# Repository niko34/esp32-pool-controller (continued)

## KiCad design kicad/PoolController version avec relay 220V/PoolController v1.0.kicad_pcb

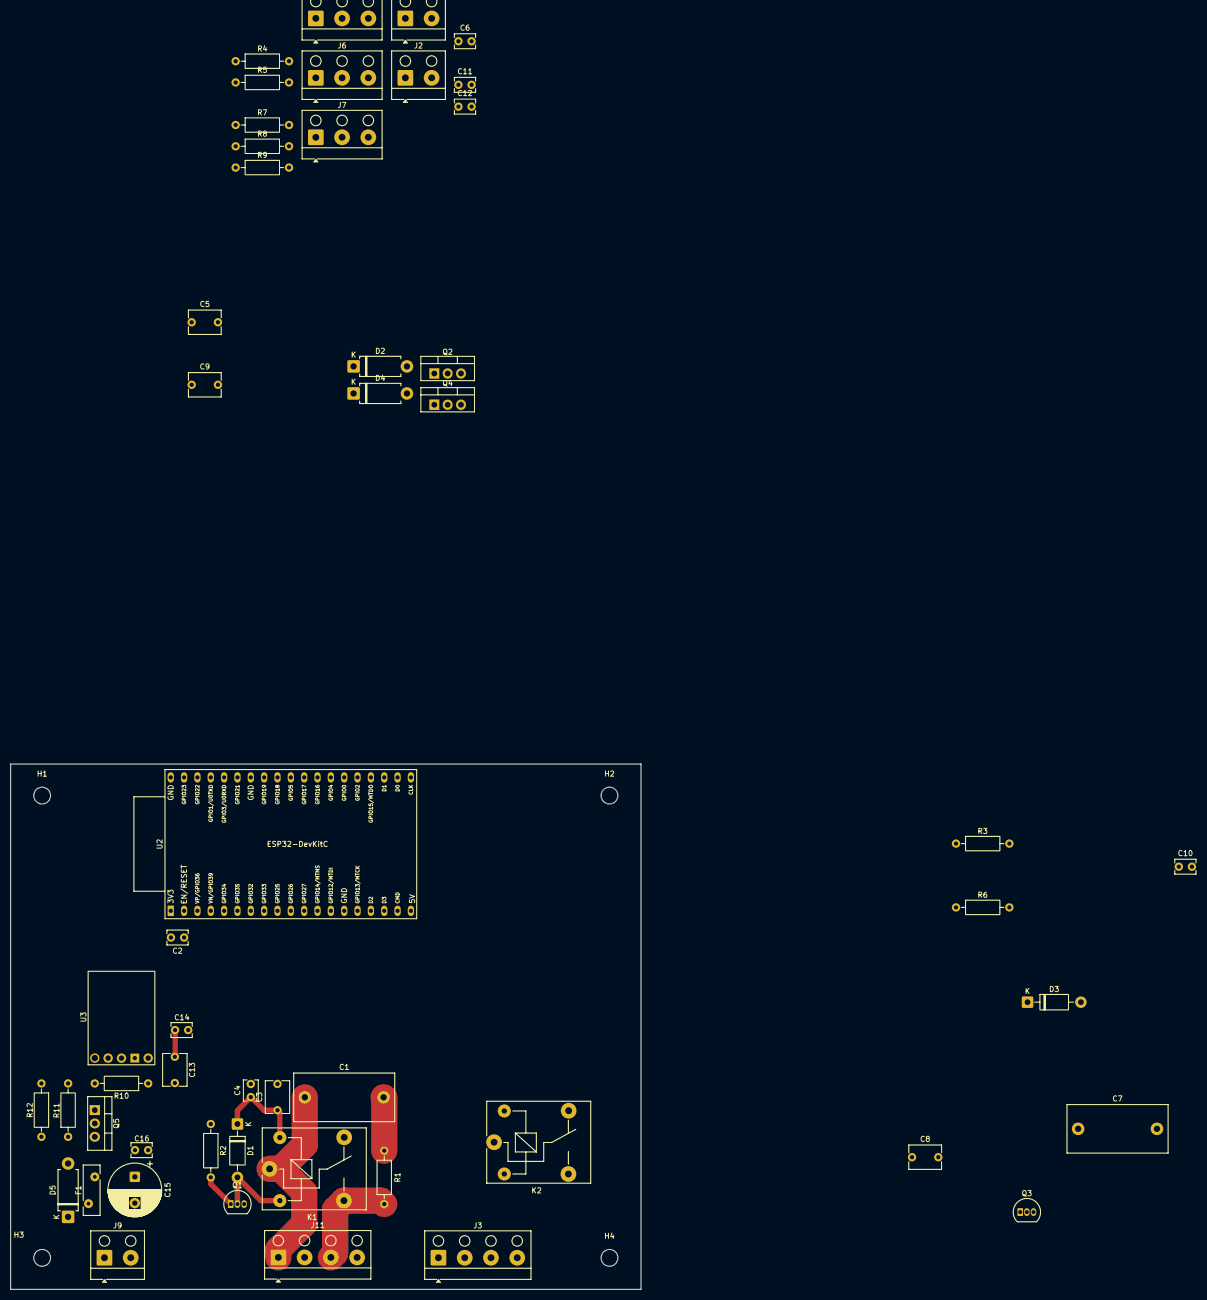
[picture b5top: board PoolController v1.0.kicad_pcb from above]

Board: 2 copper layers, 120.0 x 100.0 mm, 55 parts (0 on the bottom side), 29 nets.

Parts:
C1, C7: PME271MB6100MR30; C_Rect_L19.0mm_W9.0mm_P15.00mm_MKS4
C2, C4, C6, C10, C11, C12, C14, C16: 100nF; C_Disc_D3.8mm_W2.6mm_P2.50mm
C3, C5, C8, C9, C13: 10 µF; C_Disc_D6.0mm_W4.4mm_P5.00mm
C15: 470µF; CP_Radial_D10.0mm_P5.00mm
D1, D3: 1N4007; D_DO-41_SOD81_P10.16mm_Horizontal
D2, D4: 1N5819; D_DO-15_P10.16mm_Horizontal
D5: P6KE13A; D_DO-15_P10.16mm_Horizontal
F1: FX200-16; Fuse_Bourns_MF-RHT200
H1, H2, H3, H4: MountingHole; MountingHole_3.2mm_M3
J1, J2: Pompe Péristaltique; Altech_AK100_1x02_P5.00mm
J3, J11: Eclairage; Altech_AK100_1x04_P5.00mm
J4: Sonde température DS18B20; Altech_AK100_1x03_P5.00mm
J6, J7: Conn_01x03; Altech_AK100_1x03_P5.00mm
J9: Alimentation 12V (2A min); Altech_AK100_1x02_P5.00mm
K1, K2: SANYOU_SRD_Form_C; Relay_SPDT_SANYOU_SRD_Series_Form_C
Q1, Q3: PN2222A; TO-92_Inline
Q2, Q4: IRLZ44N; TO-220-3_Vertical
Q5: IRF4905; TO-220-3_Vertical
R1, R3, R4, R7: 100Ω; R_Axial_DIN0207_L6.3mm_D2.5mm_P10.16mm_Horizontal
R2, R6: 330Ω; R_Axial_DIN0207_L6.3mm_D2.5mm_P10.16mm_Horizontal
R5, R8, R10, R12: 10KΩ; R_Axial_DIN0207_L6.3mm_D2.5mm_P10.16mm_Horizontal
R9: 4.7KΩ; R_Axial_DIN0207_L6.3mm_D2.5mm_P10.16mm_Horizontal
R11: 10Ω; R_Axial_DIN0207_L6.3mm_D2.5mm_P10.16mm_Horizontal
U2: ESP32-DevKitC
U3: D24V10F3; Pololu_D24V10F3

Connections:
+3.3V: C2.2, C3.1, C4.1, C8.1, C10.1, C12.2, C13.1, C14.1, D1.1 (K), D3.1 (K), J4.2, J6.1, J7.1, K1.5, K2.5, R9.1, U2.1 (3V3), U3.5 (VOUT)
+12V: C5.1, C6.1, C9.1, C11.1, D2.1 (K), D4.1 (K), F1.1, J1.1, J2.1, J9.1, Q5.2 (D), R10.1, U3.3 (VIN)
/230V_IN_ECLAIRAGE: C1.1, J11.1, K1.1
/230V_IN_FILTRATION: C7.1, J3.1, K2.1
/230V_OUT_ECLAIRAGE: J11.3, K1.3, R1.1
/230V_OUT_FILTRATION: J3.3, K2.3, R3.1
/DATA_DS18B20: J4.3, R9.2, U2.5 (VDET_1/GPIO34/ADC1_CH6)
/DATA_ORP: J7.3, U2.8 (32K_XN/GPIO33/ADC1_CH5)
/DATA_PH: J6.3, U2.7 (32K_XP/GPIO32/ADC1_CH4)
/POMPE_1: R4.2, U2.15 (MTCK/GPIO13/ADC2_CH4)
/POMPE_2: R7.2, U2.12 (MTMS/GPIO14/ADC2_CH6)
/RELAIS_1: R2.1, U2.10 (DAC_2/ADC2_CH9/GPIO26)
/RELAIS_2: R6.1, U2.11 (ADC2_CH7/GPIO27)
GND: C2.1, C3.2, C4.2, C5.2, C6.2, C8.2, C9.2, C10.2, C11.2, C12.1, C13.2, C14.2, C15.2, C16.2, D5.1 (A1), J4.1, J6.2, J7.2, J9.2, Q1.3 (C), Q2.3 (S), Q3.3 (C), Q4.3 (S), R5.2, R8.2, R12.2, U2.14 (GND), U2.32 (GND), U2.38 (GND), U3.4 (GND)
unnamed: C1.2, R1.2
unnamed: C7.2, R3.2
unnamed: D1.2 (A), K1.2, Q1.2 (B)
unnamed: D2.2 (A), J1.2, Q2.2 (D)
unnamed: D3.2 (A), K2.2, Q3.2 (B)
unnamed: D4.2 (A), J2.2, Q4.2 (D)
unnamed: C15.1, C16.1, D5.2 (A2), F1.2, Q5.3 (S), R11.1
unnamed: J3.2, J3.4
unnamed: J11.2, J11.4
unnamed: Q1.1 (E), R2.2
unnamed: Q2.1 (G), R4.1, R5.1
unnamed: Q3.1 (E), R6.2
unnamed: Q4.1 (G), R7.1, R8.1
unnamed: Q5.1 (G), R11.2, R12.1
unnamed: R10.2, U3.2 (SHDN)

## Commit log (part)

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2026-04-07 chore(deps-dev): bump picomatch
    Bumps the npm_and_yarn group with 1 update in the / directory: [picomatch](https://github.com/micromatch/picomatch).
    Updates `picomatch` from 2.3.1 to 2.3.2
    - [Release notes](https://github.com/micromatch/picomatch/releases)
    - [Changelog](https://github.com/micromatch/picomatch/blob/master/CHANGELOG.md)
    - [Commits](https://github.com/micromatch/picomatch/compare/2.3.1...2.3.2)
    ---
2026-05-08 feat(ph/orp): migration Atlas EZO + outils debug oscillation (feature-021)
    Migration complète de la chaîne pH/ORP : ADS1115 + DFRobot_PH → modules
    Atlas Scientific EZO Embedded I²C (pH 0x63, ORP 0x62) sur PCB v2. Inclut
    hotfix oscillation cyclique identifiée pendant debug terrain et outils
    de diagnostic intégrés à l'UI.
    == Firmware (Atlas EZO) ==
    - src/atlas_ezo.h/cpp (NOUVEAU) : mini-classe AtlasEzoSensor. Mutex I²C
2026-05-08 chore(partitions): app à 1.5 MB / spiffs 832 KB (layout v2, ADR-0015)
    L'implémentation de feature-024 (pente sonde pH) a fait franchir la
    limite de la partition app1 (1408 KB) au firmware (1446 KB image .bin).
    Bootloader détectait CRC invalide → SW_RESET en boucle au démarrage.
    == Nouveau layout (4 MB flash) ==
    - app0 : 0x10000 → 0x180000 (1408 KB → 1536 KB, +128 KB)
    - app1 : 0x190000 → 0x180000 (1408 KB → 1536 KB, +128 KB)
2026-05-08 feat(ph): pente sonde pH Atlas EZO + chip santé sur page /ph (feature-024)
    Expose la santé de la sonde pH via la commande Atlas EZO Slope,? (pente
    acide %, pente base %, décalage zéro mV). Permet à l'utilisateur de
    diagnostiquer l'usure d'une sonde avant que la régulation devienne
    erratique. Feature strictement diagnostique : aucun impact sur canDose(),
    le PID ou le dosage.
    == Firmware ==
2026-05-08 fix(history): détection corruption LittleFS + reformatage automatique au boot
    LittleFS peut monter un filesystem corrompu sans erreur puis crasher
    en IntegerDivideByZero à la 1ère écriture (bug interne LittleFS connu,
    documenté dans le code ligne 70). Symptôme observé sur ESP32 PCB v1
    après une longue période d'inactivité — boot loop sans message
    d'erreur après "Partition historique dédiée montée".
    Le mécanisme préventif existant ne détectait que les changements de
2026-05-10 fix(sensors): underflow uint32 dans la garde 24h Slope query (feature-024)
    Sans rafraîchir `now` après _processEzoQueue() (qui peut bloquer ~900ms
    sur la commande I²C `Slope,?`), la condition de re-query 24h dans
    SensorManager::update() sous-flow en uint32 dès la 1ʳᵉ query Slope
    réussie → ré-enqueue à chaque cycle update() → spam de query Slope
    toutes les ~secondes (1 log/s observé en condition réelle).
    == Séquence du bug ==
2026-05-10 feat(debug): outil diagnostic commandes EZO + endpoint factory reset
    Ajoute 2 endpoints HTTP et une carte UI pour interroger les modules Atlas
    EZO en envoyant n'importe quelle commande arbitraire et observer la réponse
    brute. Outil indispensable pour diagnostiquer les modules qui ne répondent
    pas comme attendu (cf. analyse séquence pH/ORP feature-021).
    == Endpoints ==
    - POST /debug/ezo_command (body JSON {addr, cmd, delay_ms})
2026-05-10 fix(sensors): EZO ORP utilise R au lieu de RT,<t> (pas de payload sur ORP)
    Le firmware envoyait RT,<temp> indistinctement aux 2 modules Atlas. Sur
    l'EZO pH, RT,<t> compense la T° (Nernst) ET retourne la valeur pH compensée.
    Sur l'EZO ORP, RT,<t> est ACCEPTÉ (status=1 success) mais ne retourne PAS
    de payload (resp vide) car l'ORP est potentiométrique direct sans
    compensation T° à effectuer.
    Le firmware attendait un payload qui ne venait jamais → readSingle()
2026-05-10 fix(security): rate limit 30 → 120 req/min pour usage UI normal
    L'ancienne limite de 30 req/min était trop basse et déclenchait des
    warnings "Rate limit dépassé" en navigation normale dans l'UI :
    - Page /params ouverte : ~6-12 polls /get-config par minute
    - Page /data refresh : ~2 par minute
    - /coredump/info, autres polls : ~2-4 par minute
    - Clics utilisateur sur boutons (debug EZO notamment) : variable
2026-05-10 docs(v2.1.1): documenter les 4 fixes + outil diagnostic EZO
    Documente les 5 commits récents sur pcb-v2 :
    - 3c8b657 fix(history) détection corruption LittleFS
    - 933f17c fix(sensors) underflow uint32 slope query
    - 20e4a9b feat(debug) outil diagnostic EZO (commandes manuelles)
    - c0f2962 fix(sensors) EZO ORP utilise R au lieu de RT
    - 6c79cfc fix(security) rate limit 30 → 120 req/min
2026-05-10 fix(safety): arrêter l'injection manuelle si filtration KO + UI feedback (v2.1.2)
    Bug observé en production PCB v1 : injection manuelle volumée pH lancée
    pendant filtration active continue après l'arrêt programmé de la filtration
    → surdosage local d'acide dans la zone du retour d'eau (eau qui ne circule
    plus = corrosion + risque sanitaire).
    Validation pool-chemistry GO sous conditions, toutes appliquées.
    == Backend (src/) ==
2026-06-23 Update PCB image in README.md
    PCB update
